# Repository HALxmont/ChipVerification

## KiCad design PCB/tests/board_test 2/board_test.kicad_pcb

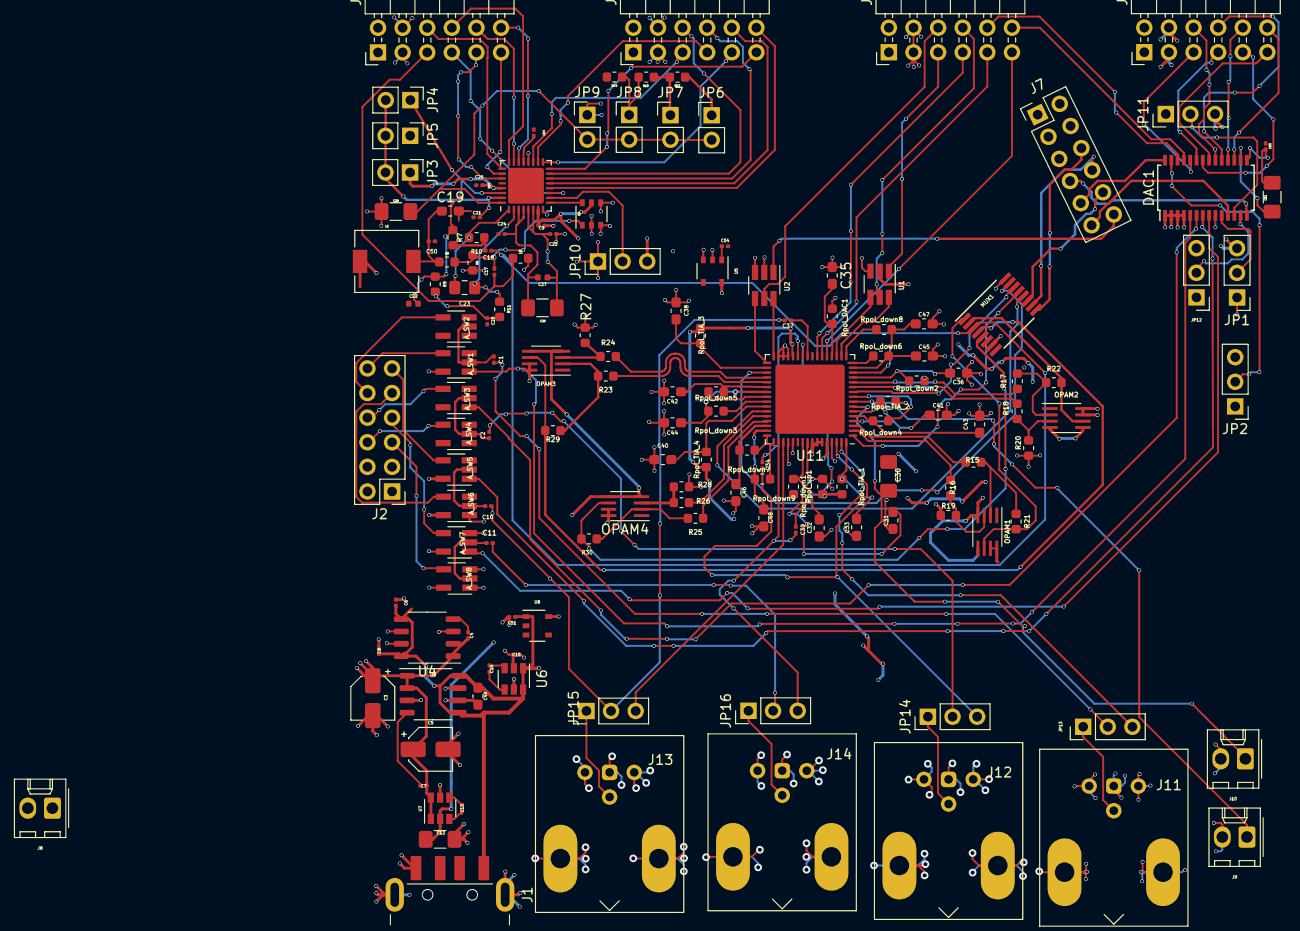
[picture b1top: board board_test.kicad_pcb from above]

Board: 4 copper layers, 151 parts (0 on the bottom side), 160 nets.

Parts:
A_SW1, A_SW2, A_SW3, A_SW4, A_SW5, A_SW6, A_SW7, A_SW8: PI5A3166; SOT-23-5_HandSoldering
C1, C2, C10, C11: 350p; C_0201_0603Metric
C3, C5: 10uF; CP_Elec_4x3
C4, C6, C7, C8, C13, C16, C24, C25, C51, C54: 1uF; C_0201_0603Metric
C9, C14, C17, C18, C20, C21, C26, C50, C53: 0.1uF; C_0201_0603Metric
C12, C52: 10uF; C_1206_3216Metric_Pad1.42x1.75mm_HandSolder
C15: 10uF; C_0201_0603Metric
C19: 4.7uF; C_0603_1608Metric_Pad1.05x0.95mm_HandSolder
C22, C27: 2.2uF; C_0402_1005Metric
C23: 12pF; C_0805_2012Metric_Pad1.15x1.40mm_HandSolder
C28, C29: 0.1uF; C_1206_3216Metric_Pad1.42x1.75mm_HandSolder
C30: 0.5uF; C_1206_3216Metric_Pad1.42x1.75mm_HandSolder
C31, C32, C33, C35, C36, C38, C40, C41, C42, C43, C44, C45, C46, C47, C48: 20uF; C_0603_1608Metric_Pad1.05x0.95mm_HandSolder
C34, C37, C39: 0.5uF; C_0201_0603Metric
C49: 10uF; C_0603_1608Metric_Pad1.05x0.95mm_HandSolder
DAC1: AD5336; TSSOP-28_4.4x9.7mm_P0.65mm
J1: USB_A; USB_A_CNCTech_1001-011-01101_Horizontal
J2, J7: Conn_02x06_Top_Bottom; PinHeader_2x06_P2.54mm_Vertical
J3, J4, J5, J6: Conn_02x06_Top_Bottom; PinHeader_2x06_P2.54mm_Horizontal
J8, J9, J10: Conn_01x02_Female; Molex_KK-254_AE-6410-02A_1x02_P2.54mm_Vertical
J11, J12, J13, J14: Conn_01x03_Male; BNC_Win_364A2x95_Horizontal
JP1: GND -> Normal op. | 3.3v -> NO data trasnfer; PinHeader_1x03_P2.54mm_Vertical
JP2: GAIN = 1 (GND) | GAIN = 2 (VDD); PinHeader_1x03_P2.54mm_Vertical
JP3, JP6: VDD; PinHeader_1x02_P2.54mm_Vertical
JP4, JP7: 2/3VDD; PinHeader_1x02_P2.54mm_Vertical
JP5, JP8: 1/3VDD; PinHeader_1x02_P2.54mm_Vertical
JP9: GND; PinHeader_1x02_P2.54mm_Vertical
JP10: Jumper_3_Bridged12; PinHeader_1x03_P2.54mm_Vertical
JP11: A0 = 0 (to GND) | A0 = 1 (to 3.3v); PinHeader_1x03_P2.54mm_Vertical
JP12: A1 = 0 (to GND) | A1 = 1 (to 3.3v); PinHeader_1x03_P2.54mm_Vertical
JP13, JP14, JP15, JP16: 350p | Detector; PinHeader_1x03_P2.54mm_Vertical
L2: L_Core_Ferrite_Small; L_6.3x6.3_H3
MUX1: DG4051E; TSSOP-16_4.4x5mm_P0.65mm
OPAM1, OPAM2, OPAM3, OPAM4: LTC6226; SSOP-8_2.95x2.8mm_P0.65mm
R5: 50; R_0603_1608Metric
R6, R7, R8, R9, R12, R13, R14: 1K; R_0603_1608Metric
R10, R11: 25; R_0603_1608Metric
R15, R16, R17, R18, R19, R20, R21, R22, R23, R24, R25, R26, R27, R28, R29, R30: 100; R_0603_1608Metric
Rpol_DAC1: 32K; R_0603_1608Metric
Rpol_TIA_1, Rpol_TIA_2, Rpol_TIA_3, Rpol_TIA_4: 973; R_0603_1608Metric
Rpol_down1: 720; R_0603_1608Metric
Rpol_down2, Rpol_down3, Rpol_down4, Rpol_down5, Rpol_down6, Rpol_down7, Rpol_down8, Rpol_down9: 100K; R_0603_1608Metric
Rpol_up1: 2.1K; R_0603_1608Metric
U1, U2: TMUX1119; SOT-23-6_Handsoldering
U3, U4: LT1763; SSOP-8_3.9x5.05mm_P1.27mm
U5, U8: NCP164ASN180T1G; TSOP-5_1.65x3.05mm_P0.95mm
U6, U7: LTC1983-3; SOT-23-6
U9: SN74AUC2G06; TSOP-6_1.65x3.05mm_P0.95mm
U10: LTC2245; QFN-32-1EP_5x5mm_P0.5mm_EP3.7x3.7mm
U11: RenzoChip; QFN-64-1EP_9x9mm_P0.5mm_EP7.15x7.15mm

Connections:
1.8vA: Rpol_TIA_1.1, Rpol_TIA_2.1, Rpol_TIA_3.1, Rpol_TIA_4.1, Rpol_up1.1, U8.5, U11.28, U11.57, U11.58, U11.59
1.8vD: U5.5, U11.53, U11.60
+3V3: C3.1, C4.2, C5.1, C7.2, C9.2, C26.2, JP1.3, JP2.3, JP3.1, JP10.3, JP11.3, JP12.3, L2.1, OPAM1.7, OPAM1.8, OPAM2.7, OPAM2.8, OPAM3.7, OPAM3.8, OPAM4.7, OPAM4.8, U3.1, U3.2, U4.1, U4.2, U7.1, U7.6, U9.5, U10.7, U10.29
+5V: C6.2, C8.2, C49.1, C51.1, J1.1, MUX1.16, U3.5, U3.8, U4.5, U4.8, U6.1, U6.6, U8.1
-3V3: C12.1, OPAM1.4, OPAM1.5, OPAM2.4, OPAM2.5, OPAM3.4, OPAM3.5, OPAM4.4, OPAM4.5, U7.2
-5V: C15.1, MUX1.7, U6.2
ADC_AIN+: C23.2, R10.2, U10.1
ADC_AIN-: C23.1, R11.1, U10.2
ADC_ANALOG_IN: C18.1, MUX1.3
ADC_CLK: U9.6, U10.9
ADC_MODE: C29.2, JP6.2, JP7.2, JP8.2, JP9.2, U10.32
ADC_REFH: C24.2, C27.2, C28.2, U10.3, U10.4
ADC_REFL: C25.2, C27.1, C28.1, U10.5, U10.6
ADC_SENSE: C21.2, JP3.2, JP4.2, JP5.2, U10.31
ADC_SHDN: JP10.2, U10.10
ADC_VCM: C22.2, JP4.1, R7.1, R9.1, U10.30
CHIP_INT_DIFF1: MUX1.1, OPAM1.6, R21.2
CHIP_INT_DIFF2: MUX1.2, OPAM2.6, R22.2
CHIP_INT_DIFF3: MUX1.4, OPAM3.6, R29.2
CHIP_INT_DIFF4: MUX1.5, OPAM4.6, R30.2
DAC_A0: DAC1.12, JP11.2
DAC_A1: DAC1.13, JP12.2
DAC_CS': DAC1.10, JP1.2
DAC_GAIN: DAC1.27, JP2.2
DAC_VOUT_A: A_SW1.1, DAC1.5
DAC_VOUT_B: A_SW3.1, DAC1.6
DAC_VOUT_C: A_SW5.1, DAC1.7
DAC_VOUT_D: A_SW7.1, DAC1.8
Detector1: J11.2, JP13.1
Detector2: J12.2, JP14.1
Detector3: J13.2, JP15.1
Detector4: J14.2, JP16.1
GND: A_SW1.3, A_SW2.1, A_SW2.3, A_SW3.3, A_SW4.1, A_SW4.3, A_SW5.3, A_SW6.1, A_SW6.3, A_SW7.3, A_SW8.1, A_SW8.3, C3.2, C5.2, C6.1, C8.1, C9.1, C12.2, C14.1, C15.2, C19.2, C20.2, C21.1, C22.1, C24.1, C25.1, C26.1, C29.1, C31.1, C32.1, C33.1, C35.1, C36.1, C38.1, C40.1, C41.2, C42.2, C43.2, C44.2, C45.2, C46.2, C47.2, C48.2, C49.2, C50.1, C51.2, C53.1, C54.2, DAC1.9, J1.4, J1.5, J2.5, J2.11, J3.5, J3.11, J4.5, J4.11, J5.5, J5.11, J6.5, J6.11, J7.5, J7.11, J8.2, J9.2, J10.2, J11.1, J11.3, J12.1, J12.3, J13.1, J13.3, J14.1, J14.3, JP1.1, JP2.1, JP9.1, JP10.1, JP11.1, JP12.1, MUX1.6, MUX1.8, R5.2, R6.2, R14.2, R19.1, R20.1, R27.1, R28.1, Rpol_DAC1.2, Rpol_down1.2, U1.3, U2.3, U3.3, U3.6, U3.7, U4.3, U4.6, U4.7, U5.2, U5.3, U6.5, U7.5, U8.2, U8.3, U9.2, U9.3, U9.4, U10.8, U10.20, U11.29, U11.30, U11.31, U11.52, U11.54, U11.61
IN_fbAmp_der_1: C43.1, Rpol_down4.1, U11.5
IN_fbAmp_der_2: C47.1, Rpol_down8.1, U11.14
IN_fbAmp_der_3: C44.1, Rpol_down5.1, U11.39
IN_fbAmp_der_4: C48.1, Rpol_down9.1, U11.47
IN_fbAmp_izq_1: C41.1, Rpol_down2.1, U11.4
IN_fbAmp_izq_2: C45.1, Rpol_down6.1, U11.15
IN_fbAmp_izq_3: C42.1, Rpol_down3.1, U11.38
IN_fbAmp_izq_4: C46.1, Rpol_down7.1, U11.46
JA1:N15: J7.1, U2.1
JA2:L14: J7.2, MUX1.11
JA3:K16: J7.3, MUX1.10
JA4:K14: J7.4, MUX1.9
JA7:N16: DAC1.11, J7.7
JA8:L15: DAC1.28, J7.8
JA9:J16: DAC1.14, J7.9
JB1:T20: DAC1.25, J5.1
JB2:U20: DAC1.26, J5.2
JB3:V20: J5.3, U1.5
JB4:W20: J5.4, U2.5
JB7:Y18: J5.7, U11.21
JB8:Y19: J5.8, U11.22
JB9:W18: J5.9, U11.23
JB10:W19: J5.10, U1.1
JC1:V15: J3.1, U10.12
JC2:W15: J3.2, U10.13
JC3:T11: J3.3, U10.14
JC4:T10: J3.4, U10.15
JC7:W14: J3.7, U10.16
JC8:Y14: J3.8, U10.17
JC9:T12: J3.9, U10.18
JC10:U12: J3.10, U10.19
JD1:T14: J6.1, U10.22
JD2:T15: J6.2, U10.23
JD3:P14: J6.3, U10.24
JD4:R14: J6.4, U10.25
JD7:U14: J6.7, U10.26
JD8:U15: J6.8, U10.27
JD9:V17: J6.9, U10.11
JD10:V18: C17.1, J6.10, R5.1
JE1:V12: DAC1.17, J4.1
JE2:W16: DAC1.18, J4.2
JE3:J15: DAC1.19, J4.3
JE4:H15: DAC1.20, J4.4
JE7:V13: DAC1.21, J4.7
JE8:U17: DAC1.22, J4.8
JE9:T17: DAC1.23, J4.9
JE10:Y17: DAC1.24, J4.10
JF1:MIO13: A_SW1.4, J2.1
JF2:MIO10: A_SW2.4, J2.2
JF3:MIO11: A_SW3.4, J2.3
JF4:MIO12: A_SW4.4, J2.4
JF7:MIO0: A_SW5.4, J2.7
JF8:MIO9: A_SW6.4, J2.8
JF9:MIO14: A_SW7.4, J2.9
JF10:MIO15: A_SW8.4, J2.10
unnamed: A_SW1.2, A_SW2.2, C1.1
unnamed: A_SW3.2, A_SW4.2, C2.1
unnamed: A_SW5.2, A_SW6.2, C10.1
unnamed: A_SW7.2, A_SW8.2, C11.1
unnamed: C4.1, U4.4
unnamed: C7.1, U3.4
unnamed: C13.1, U7.3
unnamed: C13.2, U7.4
unnamed: C16.1, U6.3
unnamed: C16.2, U6.4
unnamed: C17.2, R6.1, R8.2, U9.1
unnamed: C18.2, R7.2, R10.1
unnamed: C19.1, C50.2, L2.2, R8.1
unnamed: C20.1, R9.2, R11.2
unnamed: C52.1, DAC1.16
unnamed: JP6.1, R12.1
unnamed: JP7.1, R12.2, R13.1
unnamed: JP8.1, R13.2, R14.1
unnamed: OPAM1.2, R15.2, R21.1
unnamed: OPAM1.3, R16.1, R19.2
unnamed: OPAM2.2, R17.2, R22.1
unnamed: OPAM2.3, R18.1, R20.2
unnamed: OPAM3.2, R23.2, R29.1
unnamed: OPAM3.3, R24.1, R27.2
unnamed: OPAM4.2, R25.2, R30.1
unnamed: OPAM4.3, R26.1, R28.2
OUT_fbAmp_der_1: Rpol_down4.2, U11.9
OUT_fbAmp_der_2: Rpol_down8.2, U11.17
OUT_fbAmp_der_3: Rpol_down5.2, U11.41
OUT_fbAmp_der_4: Rpol_down9.2, U11.49
OUT_fbAmp_izq_1: Rpol_down2.2, U11.8
OUT_fbAmp_izq_2: Rpol_down6.2, U11.16
OUT_fbAmp_izq_3: Rpol_down3.2, U11.40
OUT_fbAmp_izq_4: Rpol_down7.2, U11.48
Rpol_DAC: C35.2, Rpol_DAC1.1, U11.20
Rpol_TIA_1: C33.2, Rpol_TIA_1.2, U11.64
Rpol_TIA_2: C36.2, Rpol_TIA_2.2, U11.13
Rpol_TIA_3: C38.2, Rpol_TIA_3.2, U11.34
Rpol_TIA_4: C40.2, Rpol_TIA_4.2, U11.42
Rpol_down: C32.2, Rpol_down1.1, U11.55
Rpol_up: C31.2, Rpol_up1.2, U11.56
VCC_FPGA: A_SW1.5, A_SW2.5, A_SW3.5, A_SW4.5, A_SW5.5, A_SW6.5, A_SW7.5, A_SW8.5, C14.2, C52.2, C53.2, C54.1, DAC1.1, DAC1.2, DAC1.3, DAC1.4, DAC1.15, J2.6, J2.12, J3.6, J3.12, J4.6, J4.12, J5.6, J5.12, J6.6, J6.12, J7.6, J7.12, U1.2, U2.2, U5.1, U10.21
VIN_TIA_1: C30.2, JP13.3, U11.63
VIN_TIA_1_EXT: C1.2, JP13.2
VIN_TIA_2: C34.2, JP14.3, U11.62
VIN_TIA_2_EXT: C2.2, JP14.2
VIN_TIA_3: C37.2, JP15.3, U11.51
VIN_TIA_3_EXT: C10.2, JP15.2
VIN_TIA_4: C39.2, JP16.3, U11.50
VIN_TIA_4_EXT: C11.2, JP16.2
VIN_ref_disc: J9.1, U11.6
VOUT_DAC_0: C30.1, U11.24
VOUT_DAC_1: C37.1, U11.25
VOUT_DAC_2: C34.1, U11.27
VOUT_DAC_3: C39.1, U11.26
VOUT_int_1+: R15.1, U11.3
VOUT_int_1-: R16.2, U11.2
VOUT_int_2+: R17.1, U11.12
VOUT_int_2-: R18.2, U11.11
VOUT_int_3+: R23.1, U11.37
VOUT_int_3-: R24.2, U11.36
VOUT_int_4+: R25.1, U11.45
VOUT_int_4-: R26.2, U11.44
VOU_DISC_1: U1.6, U11.18
VOU_DISC_2: U1.4, U11.19
VOU_DISC_3: U2.6, U11.32
VOU_DISC_4: U2.4, U11.33
VOU_TIA_1: MUX1.13, U11.1
VOU_TIA_2: MUX1.14, U11.10
VOU_TIA_3: MUX1.15, U11.35
VOU_TIA_4: MUX1.12, U11.43
Vadj_inv: J10.1, U11.7

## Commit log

2021-05-05 First files added
2021-05-07 Docs Update
2021-05-11 Var types PWM module update
2021-05-11 HOLD state update
2021-05-23 Files update
2021-08-27 Se han actualizado los archivos
2021-11-12 a lot of updates are up!
2022-02-10 Vivado project added
2022-03-12 ppt Defensa
